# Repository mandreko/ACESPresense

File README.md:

# ACESPresense
This repository contains KiCAD 7.0 files for a standalone PCB which allows ESPresense to run directly from AC.

## BOM
If you'd like to build this yourself, the components are listed here: 

* Electrical components: https://octopart.com/bom-tool/W4l4qdsA
* Polycase enclosure: https://www.polycase.com/pm2414

## Prebuilt
If you prefer to buy one pre-assembled, please check out my [Tindie store](https://www.tindie.com/products/30890/) for availability.

## License
<p xmlns:cc="http://creativecommons.org/ns#" >This work is licensed under <a href="http://creativecommons.org/licenses/by-sa/4.0/?ref=chooser-v1" target="_blank" rel="license noopener noreferrer" style="display:inline-block;">CC BY-SA 4.0</a></p>

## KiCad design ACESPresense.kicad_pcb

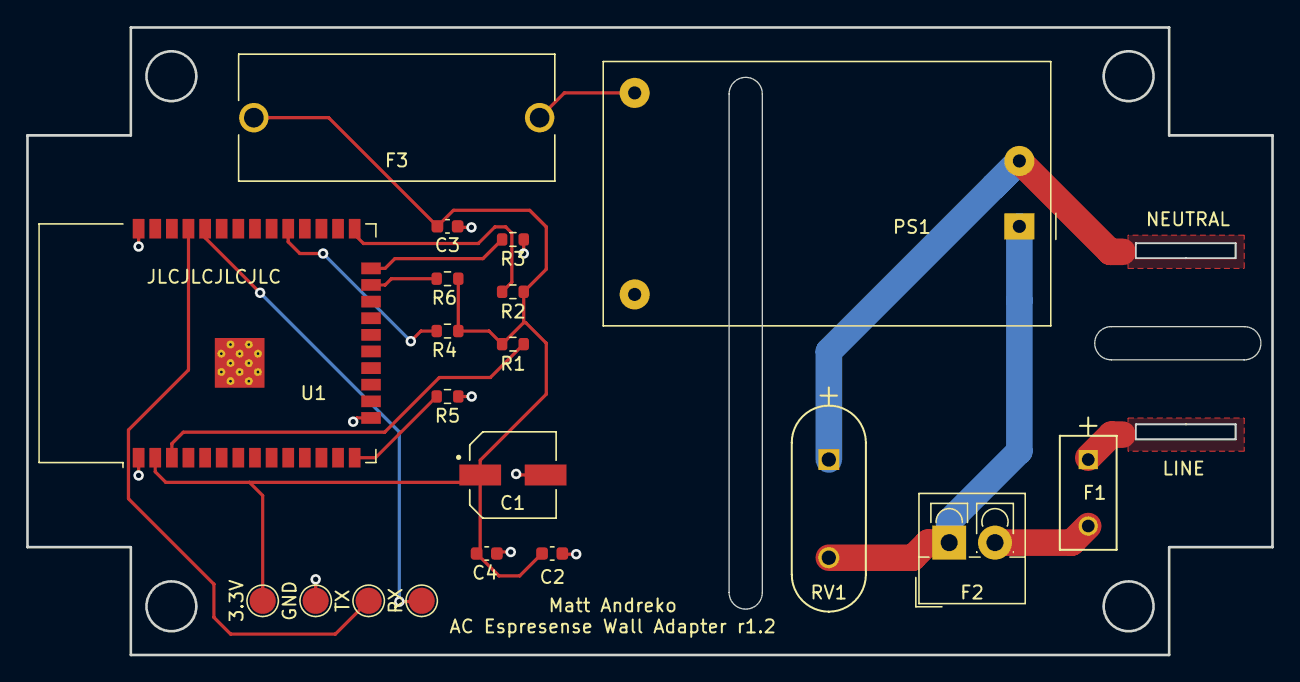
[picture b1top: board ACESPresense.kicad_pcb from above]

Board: 2 copper layers, 95.1 x 48.0 mm, 20 parts (0 on the bottom side), 14 nets.

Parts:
3.3V: TestPoint; TestPoint_Pad_D2.0mm
C1: 100u; CAP_EEEFK1C101P
C2, C4: 100n; C_0603_1608Metric
C3: 10u; C_0603_1608Metric
F1: Slow Blow Fuse; RST_BEL
F2: Thermal Fuse; TerminalBlock_4Ucon_1x02_P3.50mm_Vertical
F3: Quick Blow Fuse; FUSE_4527
GND: TestPoint; TestPoint_Pad_D2.0mm
PS1: HLK-PM03; Converter_ACDC_HiLink_HLK-PMxx
R1, R2, R3, R4, R5, R6: 10k; R_0603_1608Metric
RV1: Varistor; VARS_B72214S_15p5x5p4-7p5_TDK
RX: TestPoint; TestPoint_Pad_D2.0mm
TX: TestPoint; TestPoint_Pad_D2.0mm
U1: ESP32-WROOM-32D

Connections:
+3.3V: 3.3V.1, C1.1, C2.1, C3.1, C4.1, F3.2, R1.1, R2.2, R4.2, R6.2, U1.2 (VDD)
/EN: R1.2, U1.3 (EN)
/IO0: R2.1, U1.25 (IO0)
/RX: RX.1, U1.34 (RXD0/IO3)
/TX: TX.1, U1.35 (TXD0/IO1)
GND: C1.2, C2.2, C3.2, C4.2, GND.1, PS1.3 (-Vout), R3.2, R5.2, U1.1 (GND), U1.15 (GND), U1.38 (GND), U1.39 (GND)
NEUT: PS1.2 (AC/N), RV1.1
unnamed: F1.2, F2.2
unnamed: F3.1, PS1.4 (+Vout)
unnamed: F2.1, PS1.1 (AC/L), RV1.2
unnamed: R3.1, U1.24 (IO2)
unnamed: R4.1, U1.29 (IO5)
unnamed: R5.1, U1.14 (IO12)
unnamed: R6.1, U1.23 (IO15)

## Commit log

2023-07-06 Update README.md
    added license
2023-07-12 Added test points and fixed file names internally
2023-07-12 Update README.md
    Added Tindie store for pre-builts
2023-07-13 Update README.md
    Updated Tindie link
